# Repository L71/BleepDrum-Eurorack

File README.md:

Bleep Drum Eurorack
===================

This is the Bleep Drum by Bleep Labs (www.bleeplabs.com) converted to a Eurorack module.

It is a pretty basic adaptation with trigger and CV inputs added to make external control possible in addition to the original pad buttons and pitch knobs.

* Similar output circuitry as original, directly from DAC, 5V P-P (which is a bit lower than common in Eurorack)
* Trigger inputs are eurorack voltage compatible (positive edge trig, >1V)
* Input CVs are averaged together with knob values when plugged in (0-5V internally)  
* Power switch so it can be rebooted into noise mode independently of rack 
* The PCB layout for the RGB LED I used is wrong so the colors don't line up with the Bleep drum manual, but I don't care :) Also, this has little impact when it is just used as sound module.
* additional blinkenlights =) 

The original files and source code from Bleep Labs can be found here: https://github.com/BleepLabs/Bleep-Drum 

This module is working with the Bleep Drum MIDI firmware v12. Original Bleep Drum programmed chips should also work (but has not been tested).  

The internal drum sequencing in the module works I think - I have no original Bleep Drum to compare with - but I can't seem to get it to record or play back anything at all when the circuit sits on a breadboard (this is also why a clock output is missing).
It works fine as a sound source which was the main reason I did this anyway so I'll leave it like this. Also, the C&K switches used for the drum pads turn out to be pretty bad for playing anyway.

Panel notes: I ordered the panel from Ponoko, laser cut and engraved on 1.5mm acrylic, black surface on white core. This gives a quite nice panel, black with engraved white text on it. Not exactly bullet proof but solid enought when the PCB is attached with all jacks and additional support screws. The jacks will hold the panel 10mm above the PCB so use matching 10mm spacer bolts. 
Using a thicker panel (>2mm) is not recommended since the jack nuts will no longer fit properly.  

The module has a standard 10pin Eurorack +/- 12V power connector but it only uses the +12V and should run just fine on any DC power source that provides at least 7-8 volts if used standalone.  

Please note
===========
...that this module was developed entirely without any involvement from Bleep Labs. Whatever may be wrong with it is entirely my doing. Bleep Labs cannot be expected to answer questions about this module or anything related to it. 

The schematics, the PCB and the panel are all licensed cc-by-sa (Creative Commons Attribution-ShareAlike) 4.0.

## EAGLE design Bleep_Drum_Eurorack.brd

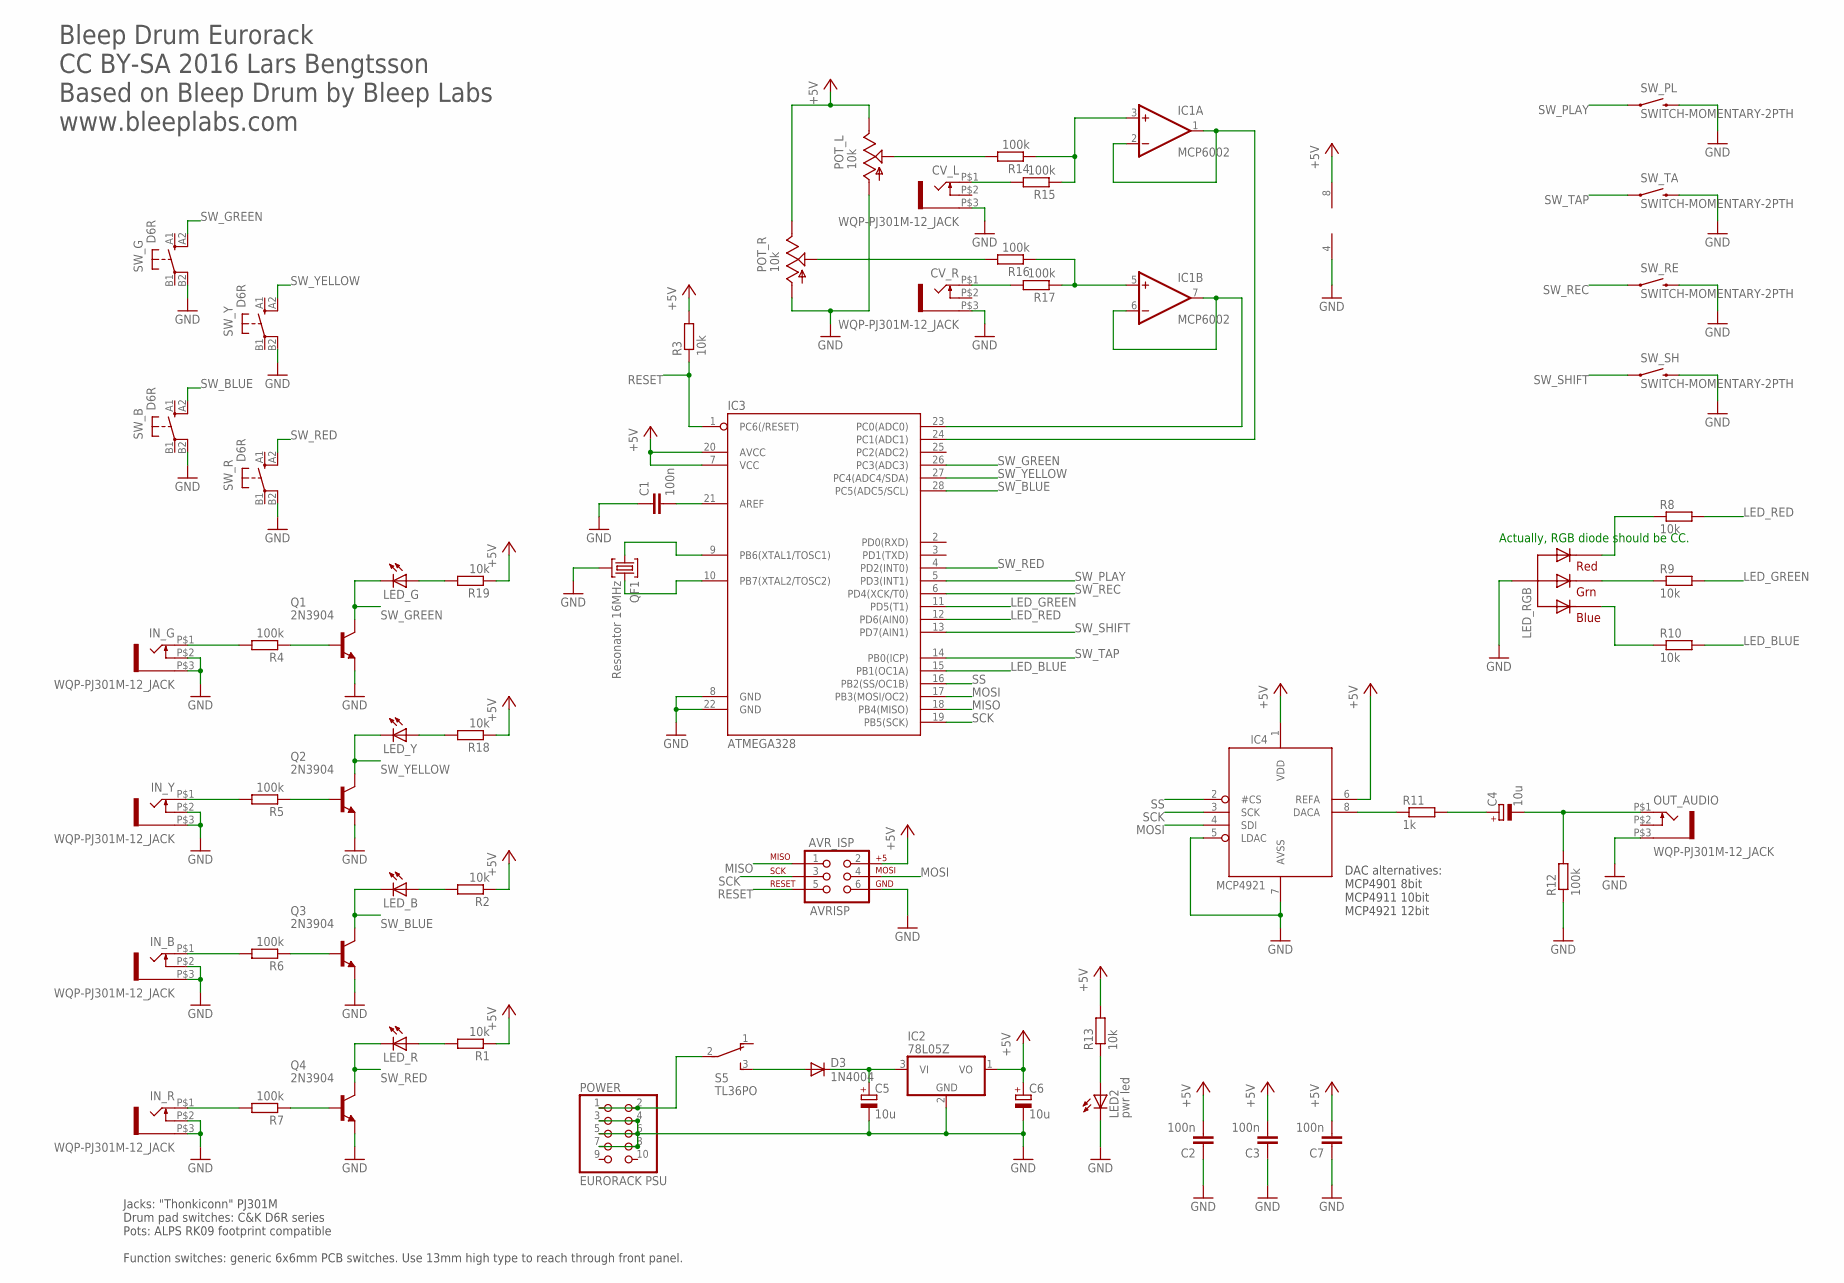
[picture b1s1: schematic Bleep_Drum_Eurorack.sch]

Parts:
AVR_ISP: AVRISP; 2X3
C1, C2, C3, C7: 100n; C025-025X050
C4, C5, C6: 10u; E2,5-5
CV_L: WQP-PJ301M-12_JACK
CV_R: WQP-PJ301M-12_JACK
D3: 1N4004; D-2.5
IC1: MCP6002; DIL08
IC2: 78L05Z; TO92
IC3: ATMEGA328; DIL28-3
IC4: MCP4921; DIL08
IN_B: WQP-PJ301M-12_JACK
IN_G: WQP-PJ301M-12_JACK
IN_R: WQP-PJ301M-12_JACK
IN_Y: WQP-PJ301M-12_JACK
LED2: pwr led; LED3MM
LED_B: LED3MM
LED_G: LED3MM
LED_R: LED3MM
LED_RGB: RGBLED_CA-5MM; LED5MMRGB
LED_Y: LED3MM
OUT_AUDIO: WQP-PJ301M-12_JACK
POT_L: 10k; ALPS_POT_VERTICAL
POT_R: 10k; ALPS_POT_VERTICAL
POWER: EURORACK PSU; 2X05
Q1, Q2, Q3, Q4: 2N3904; TO92
QF1: Resonator 16MHz; UM1
R1, R2, R3, R8, R9, R10, R13, R18, R19: 10k; 0204V
R4, R5, R6, R7, R12, R14, R15, R16, R17: 100k; 0204V
R11: 1k; 0204V
S5: TL36PO; TL3XPO
SW_B: D6R
SW_G: D6R
SW_PL: SWITCH-MOMENTARY-2PTH; TACTILE-PTH
SW_R: D6R
SW_RE: SWITCH-MOMENTARY-2PTH; TACTILE-PTH
SW_SH: SWITCH-MOMENTARY-2PTH; TACTILE-PTH
SW_TA: SWITCH-MOMENTARY-2PTH; TACTILE-PTH
SW_Y: D6R

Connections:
+5V: AVR_ISP.2, C2.2, C3.2, C6.+, C7.2, IC1.8 (V+), IC2.1 (VO), IC3.7 (VCC), IC3.20 (AVCC), IC4.1 (VDD), IC4.6 (REFA), POT_L.P$1 (E), POT_R.P$1 (E), R1.1, R2.1, R3.2, R13.2, R18.1, R19.1
+12V_IN: POWER.1, POWER.2, S5.2
GND: AVR_ISP.6, C1.1, C2.1, C3.1, C5.-, C6.-, C7.1, CV_L.P$3 (1), CV_R.P$3 (1), IC1.4 (V-), IC2.2 (GND), IC3.8 (GND), IC3.22 (GND), IC4.5 (LDAC), IC4.7 (AVSS), IN_B.P$2 (3), IN_B.P$3 (1), IN_G.P$2 (3), IN_G.P$3 (1), IN_R.P$2 (3), IN_R.P$3 (1), IN_Y.P$2 (3), IN_Y.P$3 (1), LED2.K (C), LED_RGB.2 (VCC), OUT_AUDIO.P$3 (1), POT_L.P$3 (A), POT_R.P$3 (A), POWER.3, POWER.4, POWER.5, POWER.6, POWER.7, POWER.8, Q1.3 (E), Q2.3 (E), Q3.3 (E), Q4.3 (E), QF1.2, R12.1, SW_B.B2 (P1), SW_G.B2 (P1), SW_PL.3 (2), SW_R.B2 (P1), SW_RE.3 (2), SW_SH.3 (2), SW_TA.3 (2), SW_Y.B2 (P1)
LED_BLUE: IC3.15 (PB1(OC1A)), R10.2
LED_GREEN: IC3.11 (PD5(T1)), R9.2
LED_RED: IC3.12 (PD6(AIN0)), R8.2
MISO: AVR_ISP.1, IC3.18 (PB4(MISO))
MOSI: AVR_ISP.4, IC3.17 (PB3(MOSI/OC2)), IC4.4 (SDI)
unnamed: C4.+, R11.2
unnamed: IC4.8 (DACA), R11.1
unnamed: C4.-, OUT_AUDIO.P$1 (2), R12.2
unnamed: C5.+, D3.C, IC2.3 (VI)
unnamed: IC3.9 (PB6(XTAL1/TOSC1)), QF1.1
unnamed: IC3.10 (PB7(XTAL2/TOSC2)), QF1.3
unnamed: LED_RGB.1 (RED), R8.1
unnamed: C1.2, IC3.21 (AREF)
unnamed: IN_Y.P$1 (2), R5.2
unnamed: Q2.2 (B), R5.1
unnamed: LED_R.A, R1.2
unnamed: IC1.1 (OUT), IC1.2 (-IN), IC3.24 (PC1(ADC1))
unnamed: LED_RGB.3 (GREEN), R9.1
unnamed: Q1.2 (B), R4.1
unnamed: IN_G.P$1 (2), R4.2
unnamed: LED_RGB.4 (BLUE), R10.1
unnamed: D3.A, S5.3 (S)
unnamed: Q3.2 (B), R6.1
unnamed: IN_B.P$1 (2), R6.2
unnamed: IN_R.P$1 (2), R7.2
unnamed: Q4.2 (B), R7.1
unnamed: LED2.A, R13.1
unnamed: LED_B.A, R2.2
unnamed: LED_Y.A, R18.2
unnamed: LED_G.A, R19.2
unnamed: POT_L.P$2 (S), R14.2
unnamed: IC1.3 (+IN), R14.1, R15.1
unnamed: CV_L.P$1 (2), R15.2
unnamed: POT_R.P$2 (S), R16.2
unnamed: IC1.5 (+IN), R16.1, R17.1
unnamed: CV_R.P$1 (2), R17.2
unnamed: IC1.6 (-IN), IC1.7 (OUT), IC3.23 (PC0(ADC0))
RESET: AVR_ISP.5, IC3.1 (PC6(/RESET)), R3.1
SCK: AVR_ISP.3, IC3.19 (PB5(SCK)), IC4.3 (SCK)
SS: IC3.16 (PB2(SS/OC1B)), IC4.2 (#CS)
SW_BLUE: IC3.28 (PC5(ADC5/SCL)), LED_B.K (C), Q3.1 (C), SW_B.A2 (S1)
SW_GREEN: IC3.26 (PC3(ADC3)), LED_G.K (C), Q1.1 (C), SW_G.A2 (S1)
SW_PLAY: IC3.5 (PD3(INT1)), SW_PL.1
SW_REC: IC3.6 (PD4(XCK/T0)), SW_RE.1
SW_RED: IC3.4 (PD2(INT0)), LED_R.K (C), Q4.1 (C), SW_R.A2 (S1)
SW_SHIFT: IC3.13 (PD7(AIN1)), SW_SH.1
SW_TAP: IC3.14 (PB0(ICP)), SW_TA.1
SW_YELLOW: IC3.27 (PC4(ADC4/SDA)), LED_Y.K (C), Q2.1 (C), SW_Y.A2 (S1)

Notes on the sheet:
Actually, RGB diode should be CC.
Jacks: "Thonkiconn" PJ301M Drum pad switches: C&K D6R series Pots: ALPS RK09 footprint compatible Function switches: generic 6x6mm PCB switches. Use 13mm high type to reach through front panel.
Bleep Drum Eurorack CC BY-SA 2016 Lars Bengtsson Based on Bleep Drum by Bleep Labs www.bleeplabs.com
DAC alternatives: MCP4901 8bit MCP4911 10bit MCP4921 12bit

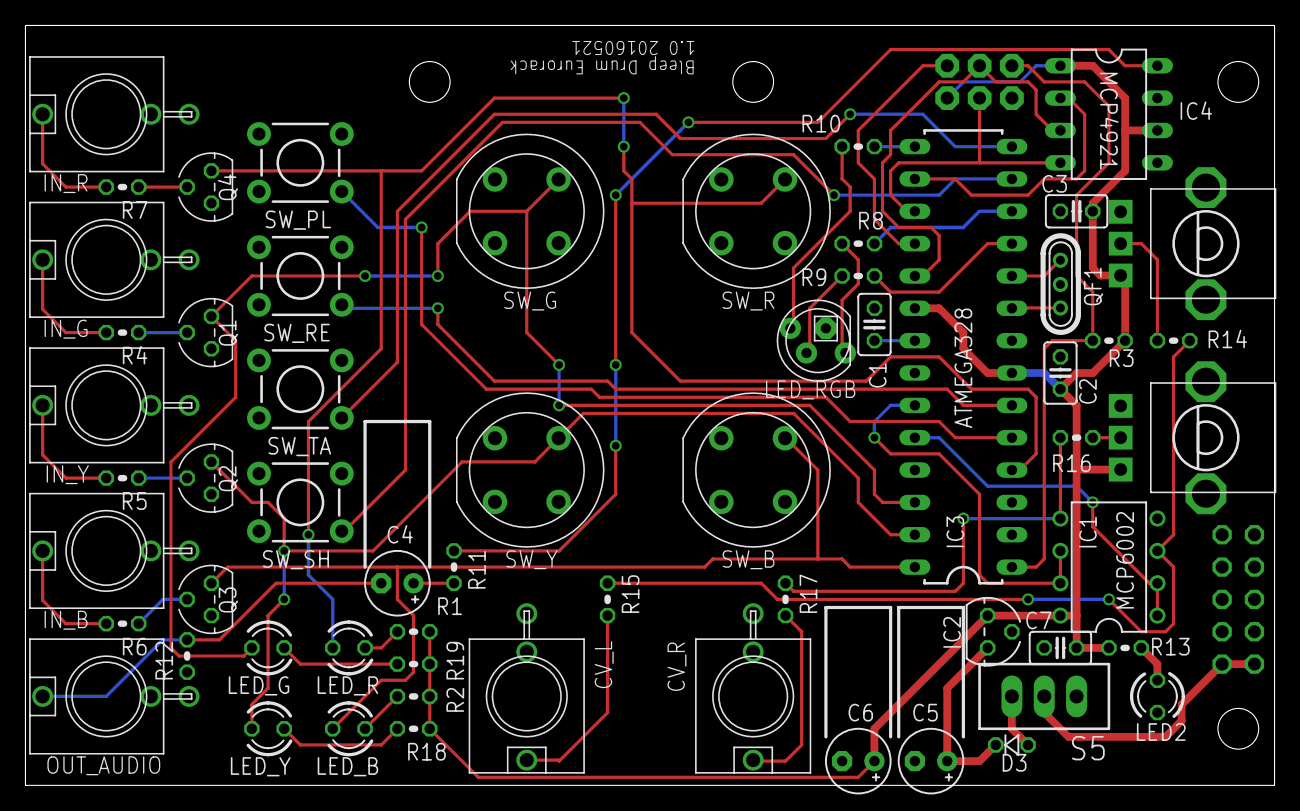
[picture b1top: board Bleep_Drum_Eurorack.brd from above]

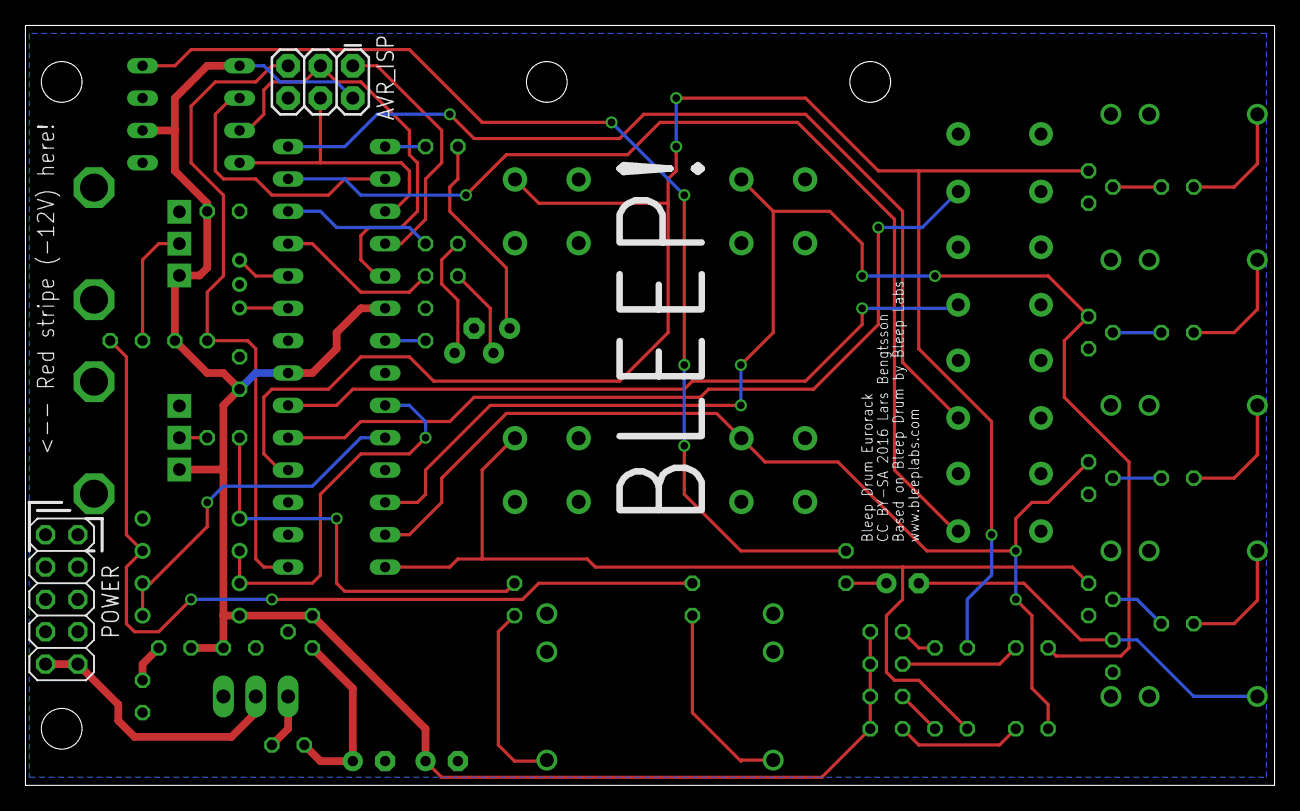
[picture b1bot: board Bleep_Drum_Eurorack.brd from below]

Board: 2 copper layers, 98.1 x 59.7 mm, 62 parts (2 on the bottom side), 51 nets.

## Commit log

2016-05-22 Initial commit of (almost) finished files.
2016-05-22 Updated info text a bit.
2016-06-12 R12=100kOhm.
2016-06-19 Moved R11 a bit. Moved a few component labels.
2016-07-27 Changed ATmega328P into ATmega328. Arduino environment seems to expect the latter type (both work fine when programmed. It's just hard to get there with a "P" type chip :) ).
2016-07-27 Added readme.
2016-07-27 Added file.
2016-07-27 Speling fixess :)
2016-07-27 Added note about switches.
2016-07-27 Some fixes.
2016-07-27 Added image.
2016-07-28 Revised text a bit.
2016-07-28 updates...
2016-07-28 ..fixes...
2016-07-29 edits...
2016-08-07 Added short info text about how to use panel drawing etc..
2016-08-08 Updated with the panel version that I actually used when ordering prototypes... (oops! :))

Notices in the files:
parts and their libraries:
SparkFun-DigitalIC: Licensing: Creative Commons ShareAlike 4.0 International - https://creativecommons.org/licenses/by-sa/4.0
